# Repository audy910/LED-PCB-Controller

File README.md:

# LED-PCB-Controller

A custom ATmega328P controller board for WS2812B addressable LED strips, designed in KiCad and built for a light box. Three buttons and a brightness knob drive three lighting modes, from adjustable warm/cool white to six animated "party" effects, all running on a standalone Arduino-compatible board with no dev board required.

## Features

- **Standalone ATmega328P** (DIP-28) running at 16 MHz, fully Arduino-compatible
- **Three lighting modes** selectable with a dedicated MODE button
- **Analog brightness control** via an on-board potentiometer, with smoothing to avoid flicker
- **Six animated effects** in Party mode: rainbow wave, color chase, twinkle, fire, bouncing ball, and meteor rain
- **EMI-hardened button input**: falling-edge detection, a confirm re-read to reject noise spikes from the LED data line, and release tracking to block repeat triggers
- **Two programming paths**: 6-pin ICSP header and FTDI serial header with DTR auto-reset
- **Through-hole only**, so it's easy to hand-solder
- **Compact 2-layer board**, roughly 44.5 × 100 mm

## Repository Contents

| File | Description |
|------|-------------|
| `Lights_For_lightbox.ino` | Arduino firmware (FastLED) |
| `LightBoxPCB.kicad_sch` | KiCad schematic |
| `LightBoxPCB.kicad_pcb` | KiCad PCB layout (2-layer) |
| `Gerbers.zip` | Fabrication-ready Gerber and drill files |

The KiCad files were saved with KiCad 10, so open them with KiCad 10 or newer.

## Controls

The **MODE** button cycles through White → Party → Color. Buttons **A** and **B** change behavior depending on the active mode. The potentiometer sets brightness in every mode.

| Mode  | Button A           | Button B      |
|-------|--------------------|---------------|
| WHITE | Warmer             | Cooler        |
| PARTY | Next effect preset | Shift color   |
| COLOR | Toggle auto-cycle  | Step hue      |

## Hardware

### Pin Map

| ATmega328P Pin | Arduino Pin | Function |
|----------------|-------------|----------|
| PD6 (pin 12)   | D6          | LED data out (through 470 Ω series resistor) |
| PC0 (pin 23)   | A0          | Brightness potentiometer wiper |
| PD2 (pin 4)    | D2          | MODE button (to GND, internal pull-up) |
| PD3 (pin 5)    | D3          | Button A (to GND, internal pull-up) |
| PD4 (pin 6)    | D4          | Button B (to GND, internal pull-up) |
| PD0 / PD1      | D0 / D1     | FTDI serial RX / TX |
| PB3 / PB4 / PB5 | D11 / D12 / D13 | ICSP MOSI / MISO / SCK |

### Connectors

| Ref | Type | Pinout |
|-----|------|--------|
| J3  | Barrel jack | 5 V power input |
| J4  | 1×3 header  | LED strip: 5V, DATA, GND |
| J1  | 2×3 header  | ICSP (standard AVR pinout) |
| J2  | 1×6 header  | FTDI: GND, CTS (n/c), VCC, TX, RX, DTR |

### Bill of Materials

| Ref | Value | Footprint |
|-----|-------|-----------|
| U1 | ATmega328P-P | DIP-28 |
| CLK1 | 16 MHz crystal | HC49-4H |
| C4, C5 | 22 pF | Ceramic disc, 5 mm pitch |
| C1, C2, C3, C6, C7 | 100 nF | Ceramic disc, 5 mm pitch |
| C8 | 10 µF | Radial electrolytic, 5 mm dia. |
| C9 | 1000 µF | Radial electrolytic, 10 mm dia. |
| R1 | 10 kΩ | Axial (reset pull-up) |
| R2 | 470 Ω | Axial (LED data series resistor) |
| RV1 | Potentiometer | Alps RK09L, vertical |
| BTN_MODE1, BTN_A1, BTN_B1 | Tactile switch | 12 mm THT |
| J1 | 2×3 pin header | 2.54 mm |
| J2 | 1×6 pin header | 2.54 mm |
| J3 | Barrel jack | Würth 6941xx301002 |
| J4 | 1×3 pin header | 2.54 mm |

### Design Notes

- **Decoupling:** 100 nF caps on VCC and AVCC, a 100 nF cap on AREF, a 10 µF bulk cap near the MCU, and a 1000 µF reservoir cap on the 5 V rail to absorb inrush current when the strip powers up or changes brightness quickly.
- **LED data line:** the 470 Ω series resistor damps ringing and protects the first LED's data input.
- **Auto-reset:** DTR on the FTDI header couples to RESET through a 100 nF cap, so uploads over serial work like a normal Arduino.

## Power

The barrel jack feeds the 5 V rail directly. There's no on-board regulator, so use a **regulated 5 V supply**. Feeding it 9 V or 12 V will damage the MCU and the LEDs.

Each WS2812B can draw up to about 60 mA at full white. The default 11-LED configuration needs up to about 0.66 A, so a 5 V / 1 A supply is plenty. Scale the supply up if you increase `NUM_LEDS`.

## Fabrication and Assembly

1. Upload `Gerbers.zip` directly to a PCB fab (JLCPCB, PCBWay, OSH Park, etc.). The defaults are fine: 2 layers, 1.6 mm, HASL.
2. Solder components from shortest to tallest: resistors, ceramic caps, crystal, IC socket (recommended for the DIP-28), headers, electrolytics, buttons, potentiometer, barrel jack.
3. Watch the polarity on C8 and C9.
4. Before inserting the ATmega328P, power the board and check for 5 V between VCC and GND on the socket.

## Firmware

### Dependencies

- [Arduino IDE](https://www.arduino.cc/en/software) or Arduino CLI
- [FastLED](https://github.com/FastLED/FastLED) library (install via Library Manager)

### Configuration

Edit these defines at the top of `Lights_For_lightbox.ino` to match your setup:

```cpp
#define NUM_LEDS       11     // number of LEDs on your strip
#define COLOR_ORDER    GRB    // change if colors look swapped
#define DEBOUNCE_MS    600    // raise if buttons still double-trigger
#define CONFIRM_MS     12     // noise-rejection re-check delay
```

### Flashing

Set the board to **Arduino Uno** (ATmega328P, 16 MHz). Then use one of these methods.

**Option A: ICSP (blank chip)**
1. Connect an ISP programmer (USBasp, or another Arduino running the *ArduinoISP* sketch) to J1.
2. Run **Tools → Burn Bootloader** once to set the fuses for the 16 MHz external crystal.
3. Upload with **Sketch → Upload Using Programmer**, or switch to Option B now that the bootloader is installed.

**Option B: FTDI (bootloader installed)**
1. Connect a 5 V FTDI adapter to J2, matching GND to GND.
2. Select the adapter's port and click **Upload**. DTR resets the chip automatically.

You can also flash the chip in an Arduino Uno and move it to the board.

## Troubleshooting

| Symptom | Likely cause and fix |
|---------|----------------------|
| Buttons trigger on their own | EMI from the LED data line. Raise `DEBOUNCE_MS` (e.g. 800) and keep the LED cable away from the button wiring. |
| LEDs flicker or reset at high brightness | Supply can't keep up. Use a beefier 5 V supply and confirm C9 is installed. |
| Wrong colors (e.g. red shows as green) | Change `COLOR_ORDER` to `RGB` or `BRG`. |
| Upload fails over FTDI | Bootloader not installed (use Option A first), TX/RX swapped, or the adapter is set to 3.3 V. |
| Board doesn't run after burning bootloader | Check the crystal and its 22 pF load caps. |

## Author

**Audrey** — Computer Engineering, UC Riverside

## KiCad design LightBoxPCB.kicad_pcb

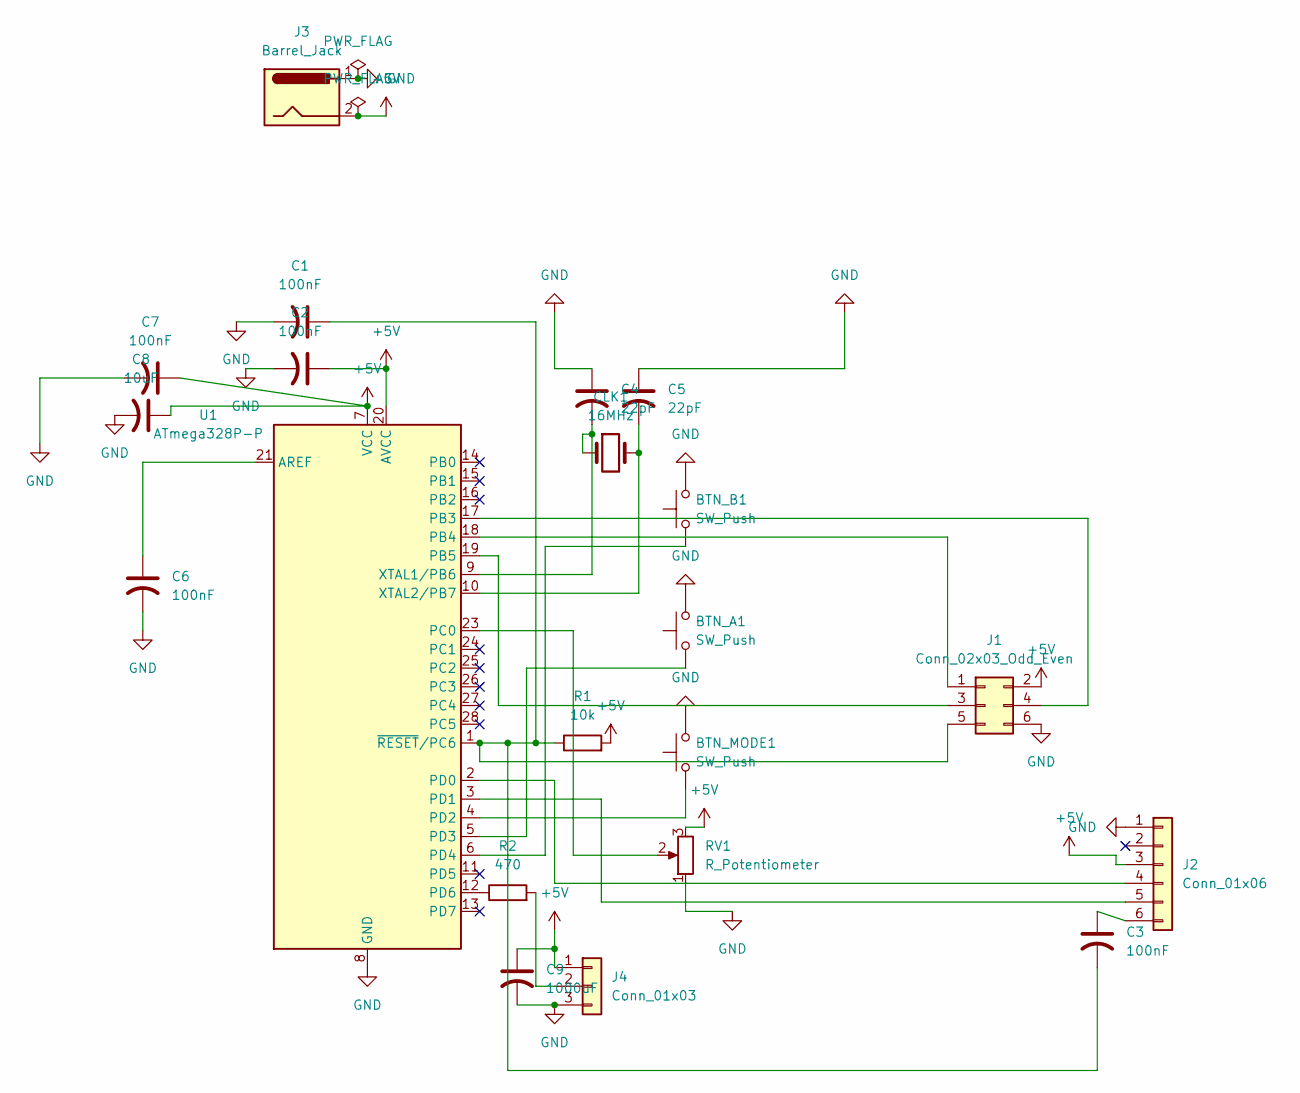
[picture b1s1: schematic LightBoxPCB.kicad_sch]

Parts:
BTN_A1: SW_Push; SW_PUSH-12mm
BTN_B1: SW_Push; SW_PUSH-12mm
BTN_MODE1: SW_Push; SW_PUSH-12mm
C1, C2, C3, C6, C7: 100nF; C_Disc_D5.0mm_W2.5mm_P5.00mm
C4, C5: 22pF; C_Disc_D5.0mm_W2.5mm_P5.00mm
C8: 10uF; CP_Radial_D5.0mm_P2.50mm
C9: 1000uF; CP_Radial_D10.0mm_P5.00mm
CLK1: 16MHz; Crystal_HC49-4H_Vertical
J1: Conn_02x03_Odd_Even; PinHeader_2x03_P2.54mm_Vertical
J2: Conn_01x06; PinHeader_1x06_P2.54mm_Vertical
J3: Barrel_Jack; BarrelJack_Wuerth_6941xx301002
J4: Conn_01x03; PinHeader_1x03_P2.54mm_Vertical
R1: 10k; R_Axial_DIN0207_L6.3mm_D2.5mm_P10.16mm_Horizontal
R2: 470; R_Axial_DIN0207_L6.3mm_D2.5mm_P10.16mm_Horizontal
RV1: R_Potentiometer; Potentiometer_Alps_RK09L_Single_Vertical
U1: ATmega328P-P; DIP-28_W7.62mm

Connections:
+5V: C2.1, C7.1, C8.1, C9.1, J1.2, J2.3, J3.2, J4.1, R1.2, RV1.3, U1.7 (VCC), U1.20 (AVCC)
GND: BTN_A1.2, BTN_B1.2, BTN_MODE1.2, C1.2, C2.2, C4.1, C5.1, C6.2, C7.2, C8.2, C9.2, J1.6, J2.1, J3.1, J4.3, RV1.1, U1.8 (GND), U1.22 (GND)
unnamed: J1.1, U1.18 (PB4)
unnamed: J1.3, U1.19 (PB5)
unnamed: J1.4, U1.17 (PB3)
unnamed: C1.1, C3.2, J1.5, R1.1, U1.1 (~RESET/PC6)
unnamed: J2.4, U1.2 (PD0)
unnamed: J2.5, U1.3 (PD1)
unnamed: C3.1, J2.6
unnamed: J4.2, R2.2
unnamed: C6.1, U1.21 (AREF)
unnamed: RV1.2, U1.23 (PC0)
unnamed: BTN_MODE1.1, U1.4 (PD2)
unnamed: BTN_A1.1, U1.5 (PD3)
unnamed: BTN_B1.1, U1.6 (PD4)
unnamed: R2.1, U1.12 (PD6)
unnamed: C4.2, CLK1.1, U1.9 (XTAL1/PB6)
unnamed: C5.2, CLK1.2, U1.10 (XTAL2/PB7)

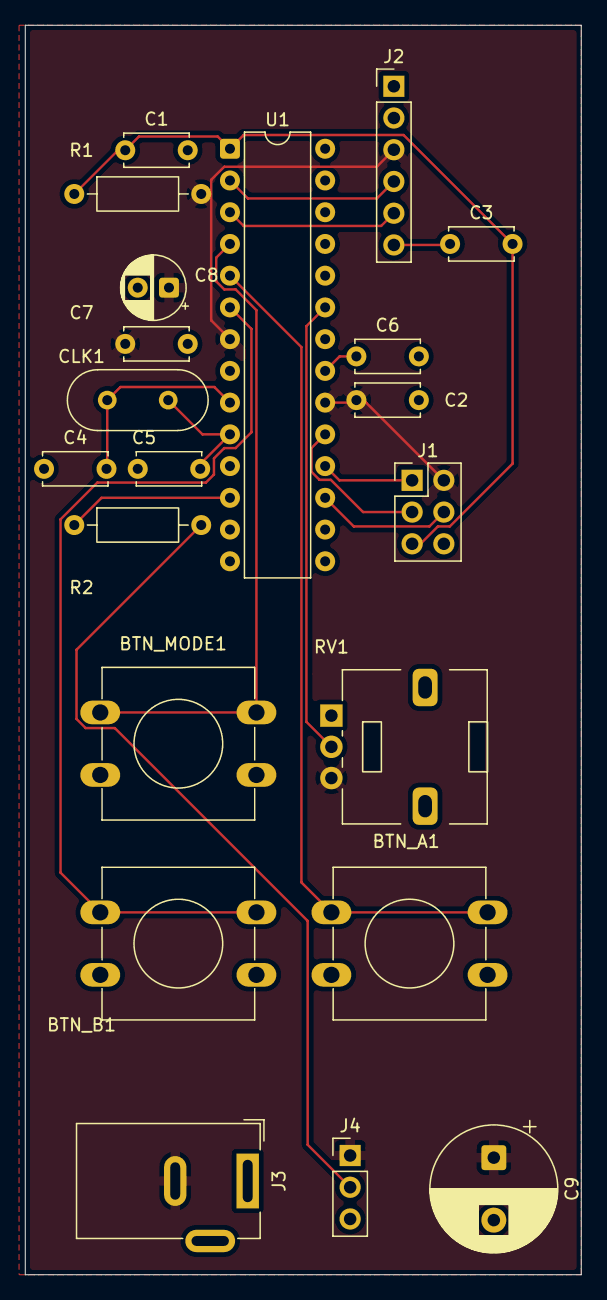
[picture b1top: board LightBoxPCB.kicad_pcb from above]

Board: 2 copper layers, 44.5 x 100.0 mm, 21 parts (0 on the bottom side), 18 nets.
